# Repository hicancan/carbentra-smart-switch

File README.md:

# CARBENTRA Switch · 三路智能灯光开关

面向普通照明的三路独立远程通断工程候选。保留本地按键，使用 Wi-Fi 连接 MQTT，蓝牙负责安全配网；计量三路灯具的合计用电。外观参考用户提供的白色圆角三键开关图片，内部结构、电路和固件为独立设计。

## 从这里开始

- **构建验证**：[LOCAL_BUILD.md](LOCAL_BUILD.md)，PowerShell 7 / uv Python 3.12 / MSVC / KiCad 10 / Blender 5.2 / ESP-IDF 5.4.3。
- **改外壳**：`mechanical/` 的可编辑 Blender 源文件与参数化生成脚本
- **改电路**：KiCad 10 打开 `electronics/power.kicad_pro` 或 `electronics/control.kicad_pro`
- **查元器件**：`electronics/bom.csv`、`pinmap.csv`、`mechanical_interface.json`
- **制造与展示**：[GitHub Releases](https://github.com/hicancan/carbentra-smart-switch/releases) 提供 Gerber/钻孔、GLB/STL、图片/PDF/视频与默认禁止吸合的开发固件。
- **继续固件**：[固件说明](firmware/README.md)、[协议与条件](docs/firmware.md)、[实际目标构建报告](firmware/build-report.json)
- **安全修复复验**：[本次固件修复报告](firmware/remediation-report.json)：证书日期配置、实际 ESP32-C3 编译负控与独立 host 证书负控；不代替实物 TLS 握手或现场安全验证
- **了解电气前提**：[电路说明](docs/electronics.md)、[结构说明](mechanical/README.md)

## 已实现的范围

- 三路控制、本地按键防抖、开机先释放、上电OFF；工程构建默认禁止继电器吸合，独立编译放行与逐台commissioning后才允许ON
- 每通道15分钟手动保持、保护/维护/故障守卫，真实本地输入与独立sample序号；网络不能隐式覆盖本地保持
- Wi-Fi 与双向 TLS MQTT 远程命令；时效、序列及幂等处理
- 官方 BLE Security 2 配网，需独立的设备工厂配置；没有内嵌通用密码
- MCP39F511A 串口计量读取、校验与累计能量保存；校准缺失、数据过期或异常时不伪造读数
- 实际 ESP-IDF 5.4.3 / ESP32-C3 目标构建通过，具体结果与源/产物哈希见构建报告

共享设备语义与运行时以 [carbentra-campus-platform](https://github.com/hicancan/carbentra-campus-platform) 的 `packages/iot-contract` 和 `edge` 为唯一实现；lighting-1..3 映射为 relay.1..3，合计电量只计一次。本次 Windows 原生编译、主机回归、ERC/DRC、网络连通、8 mm 隔离与八条主电流路径检查见[验证摘要](verification/local-validation.json)。

可生成的大文件已移出 Git，构建只写指定的外部目录。电路复现边界为原生 KiCad → 严格检查 → 制造输出；旧一次性生成与自动布线工具退入 Git 历史，不承诺重新自动布线得到相同 PCB。

蓝牙在本版本中用于配网，并非另一个直接开关灯协议。计量对象是三路照明合计，不提供单路电量；开关自身待机耗电不在这条分流测量通路内。继电器软件输出状态不等于实际触点或灯具状态的独立回读。

## 尺寸与安装假设

参考图没有确认厂商型号或官方尺寸。本设计提出 86 × 86 mm 面板、9.8 mm 前部突出、74 × 70 × 34 mm 后盒，总包络为 86 × 86 × 43.8 mm。需要根据实际墙腔、螺钉与导线弯曲空间核对，不能当作所有“86底盒”通用安装承诺。

电气方案假设开关盒中具备零线，采用 220–240 V AC、50 Hz 输入。不包含单火线、调光或调色温方案；不需要把灯具回流零线接回该开关盒。

## 使用边界

这是未上电、未安装、未经过实物验证的工程文件。规则检查和成功编译不等同于电气安全、温升、浪涌、EMC、射频、灯具启动冲击或计量精度认证。制造输出不是量产放行文件，需由合格人员完成器件、装配及样机验证。

仅针对普通照明研究，不用于消防应急或其他安全关键照明。远程 OFF 不构成维修隔离；一次保护元件和最终负载能力必须按现场条件验证。

许可证范围见 [LICENSES.md](LICENSES.md)。本地 KiCad 库、SDK、厂商资料继续遵守各自许可；参见 [电路第三方说明](electronics/THIRD_PARTY.md)和[固件第三方说明](firmware/THIRD_PARTY_NOTICES.md)。

本次 Windows 固件与发布回归见 [当前固件验证](verification/current-firmware-validation.json)。打包要求当前来源和实际目标字节一致；历史 CAD/媒体复用独立标注，未重新运行实物、CAD 或渲染验收。

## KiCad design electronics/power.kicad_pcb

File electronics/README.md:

# Native editable electronics

Open the control / power `.kicad_pro` projects with KiCad 10.0.5. Schematics, routed boards, rules, local symbol/footprint libraries, BOM, pin maps and mechanical contracts are retained as editable source. These native circuit files are authoritative.

Follow [LOCAL_BUILD.md](../LOCAL_BUILD.md) and `scripts/dev.ps1 -Action electronics -BuildRoot <external-directory>`. The coordinator copies source into a fresh external directory, runs strict ERC/DRC, exports native netlists and independently compares PCB pad connections, then produces schematic PDF, Gerbers, Excellon drills and source-faithful presentation sheets. A nonzero rule check stops the workflow. Generated output and detailed JSON reports live in the build tree and Release bundle.

The export workflow also checks isolated hot/cold copper spacing and eight selected main current paths. These geometrical checks do not establish a load rating or electrical safety certification.

The validated reproducible boundary is native circuit → checks → manufacturing outputs. Earlier one-time ECO, placement-generation and autorouting scripts are retained only in Git history. Their alternate valid routings are not claimed to reproduce the current boards. After deliberate native edits, rerun the whole electronics stage and review the resulting drawings.

Third-party datasheets are linked in `reference-sources.json` and BOM/documentation rather than redistributed. Retained library files preserve their original attribution. See [THIRD_PARTY.md](THIRD_PARTY.md).

Engineering candidate only: no fabricated-board inspection, powered measurements, RF/thermal qualification or manufacturing release is implied.

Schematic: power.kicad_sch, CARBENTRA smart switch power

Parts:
C1, C2, C3, C4: 33n; C_0603_1608Metric
C5: 1u; C_0603_1608Metric
C6, C7, C8, C9, C10, C12, C14: 100n; C_0603_1608Metric
C11, C13: 10u; C_0805_2012Metric
C15: 220u 6.3V; CP_Elec_6.3x5.8
C16: 100u 10V; CP_Elec_6.3x5.8
D1, D2, D3: SS14; D_SMA
F1: T2A 277VAC / 1500A BC; UMT_H
J1: L N L1 L2 L3; TerminalBlock_Phoenix_MKDS-1,5-5-5.08_1x05_P5.08mm_Horizont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
J2: COLD LINK / JST-PH8; JST_PH_B8B-PH-K_1x08_P2.00mm_Vertical
K1, K2, K3: G5Q-1A DC5; Relay_SPST_Omron-G5Q-1A
PS1: RAC05-05SK/277; RAC05_05SK_277
Q1, Q2, Q3: AO3400A; SOT-23
R1, R2, R3: 100R; R_0603_1608Metric
R4, R5, R6: 100k; R_0603_1608Metric
R7: 2mR 4-terminal Kelvin; R_Shunt_Vishay_WSK2512_6332Metric_T2.21mm
R8, R9, R10, R15: 1k; R_0603_1608Metric
R11, R12, R13, R14: 249k; R_1206_3216Metric
R16: 10R; R_0603_1608Metric
R17, R18: 10k; R_0603_1608Metric
RV1: TMOV14RP275E; TMOV14
U2: MCP39F511A-E/MQ; QFN-28-1EP_5x5mm_P0.5mm_EP3.25x3.25mm
U3: ISOW7821DWER; ISOW7821_DWE

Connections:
C_3V3: C13.1, C14.1, C15.1, J2.3 (3V3), U3.1 (VCC), U3.7 (EN1)
C_5V: C16.1, D1.1 (K), D2.1 (K), D3.1 (K), J2.1 (5V), K1.5, K2.5, K3.5, PS1.7 (5V)
C_COIL1: D1.2 (A), K1.1, Q1.3 (D)
C_COIL2: D2.2 (A), K2.1, Q2.3 (D)
C_COIL3: D3.2 (A), K3.1, Q3.3 (D)
C_GATE1: Q1.1 (G), R1.2, R4.1
C_GATE2: Q2.1 (G), R2.2, R5.1
C_GATE3: Q3.1 (G), R3.2, R6.1
C_GND: C13.2, C14.2, C15.2, C16.2, J2.2 (GND), PS1.9 (GND_COLD), Q1.2 (S), Q2.2 (S), Q3.2 (S), R4.2, R5.2, R6.2, U3.2 (GND1), U3.8 (GND1)
C_RELAY1: J2.4 (RLY1), R1.1
C_RELAY2: J2.5 (RLY2), R2.1
C_RELAY3: J2.6 (RLY3), R3.1
C_UART_RX: J2.8 (RX), U3.4 (OUTB)
C_UART_TX: J2.7 (TX), U3.3 (INA)
H_3V3: C7.1, C11.1, C12.1, R16.1, R17.1, R18.1, U2.25 (DVDD), U3.16 (VISO)
H_AVDD: C5.1, C6.1, R16.2, U2.11 (AVDD)
H_COMMON: U2.5 (COMMONA), U2.13 (COMMONB)
H_DIV1: R11.2, R12.1
H_DIV2: R12.2, R13.1
H_DIV3: R13.2, R14.1
H_GND: C1.2, C2.2, C3.2, C4.2, C5.2, C6.2, C7.2, C8.2, C9.2, C10.2, C11.2, C12.2, F1.2, PS1.5 (AC_L), R7.1 (I_IN), R10.1, R15.2, RV1.2 (NEUTRAL), U2.20 (AN_IN), U2.21 (AGND), U2.24 (DGND), U2.27 (DGND), U2.29 (EP), U3.9 (GND2), U3.11 (SEL), U3.15 (GND2)
H_IM: C2.1, R9.2, U2.17 (I-)
H_IP: C1.1, R8.2, U2.16 (I+)
H_KELVIN_IN: R7.2 (S_IN), R9.1
H_KELVIN_OUT: R7.3 (S_OUT), R8.1
H_LOAD: K1.2, K2.2, K3.2, R7.4 (I_OUT)
H_MCLR: C10.1, R18.2, U2.26 (MCLR_N)
H_REF: C8.1, U2.23 (REF)
H_RESET: C9.1, R17.2, U2.10 (RESET_N)
H_RX: U2.4 (RX), U3.14 (OUTA)
H_TX: U2.12 (TX), U3.13 (INB)
H_VM: C3.1, R10.2, U2.18 (V-)
H_VP: C4.1, R14.2, R15.1, U2.19 (V+)
L_IN: F1.1, J1.1 (L)
L_OUT1: J1.3 (L1), K1.3
L_OUT2: J1.4 (L2), K2.3
L_OUT3: J1.5 (L3), K3.3
N_IN: J1.2 (N), PS1.1 (AC_N), R11.1, RV1.1 (LINE)

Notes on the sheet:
01 / MAINS + PROTECTION + ISOLATED PSU
02 / THREE INDEPENDENT RELAYS + DRIVERS
03 / AGGREGATE METER + REINFORCED BARRIER
CARBENTRA / SMART LIGHT SWITCH / POWER / A-CANDIDATE
DEVELOPMENT ONLY: neutral 220VAC / no dimming / no physical contact feedback / never energize this unqualified prototype
H_* is LIVE-domain. C_* is isolated control. No ground tie across barrier. ERC/DRC do not qualify mains safety.

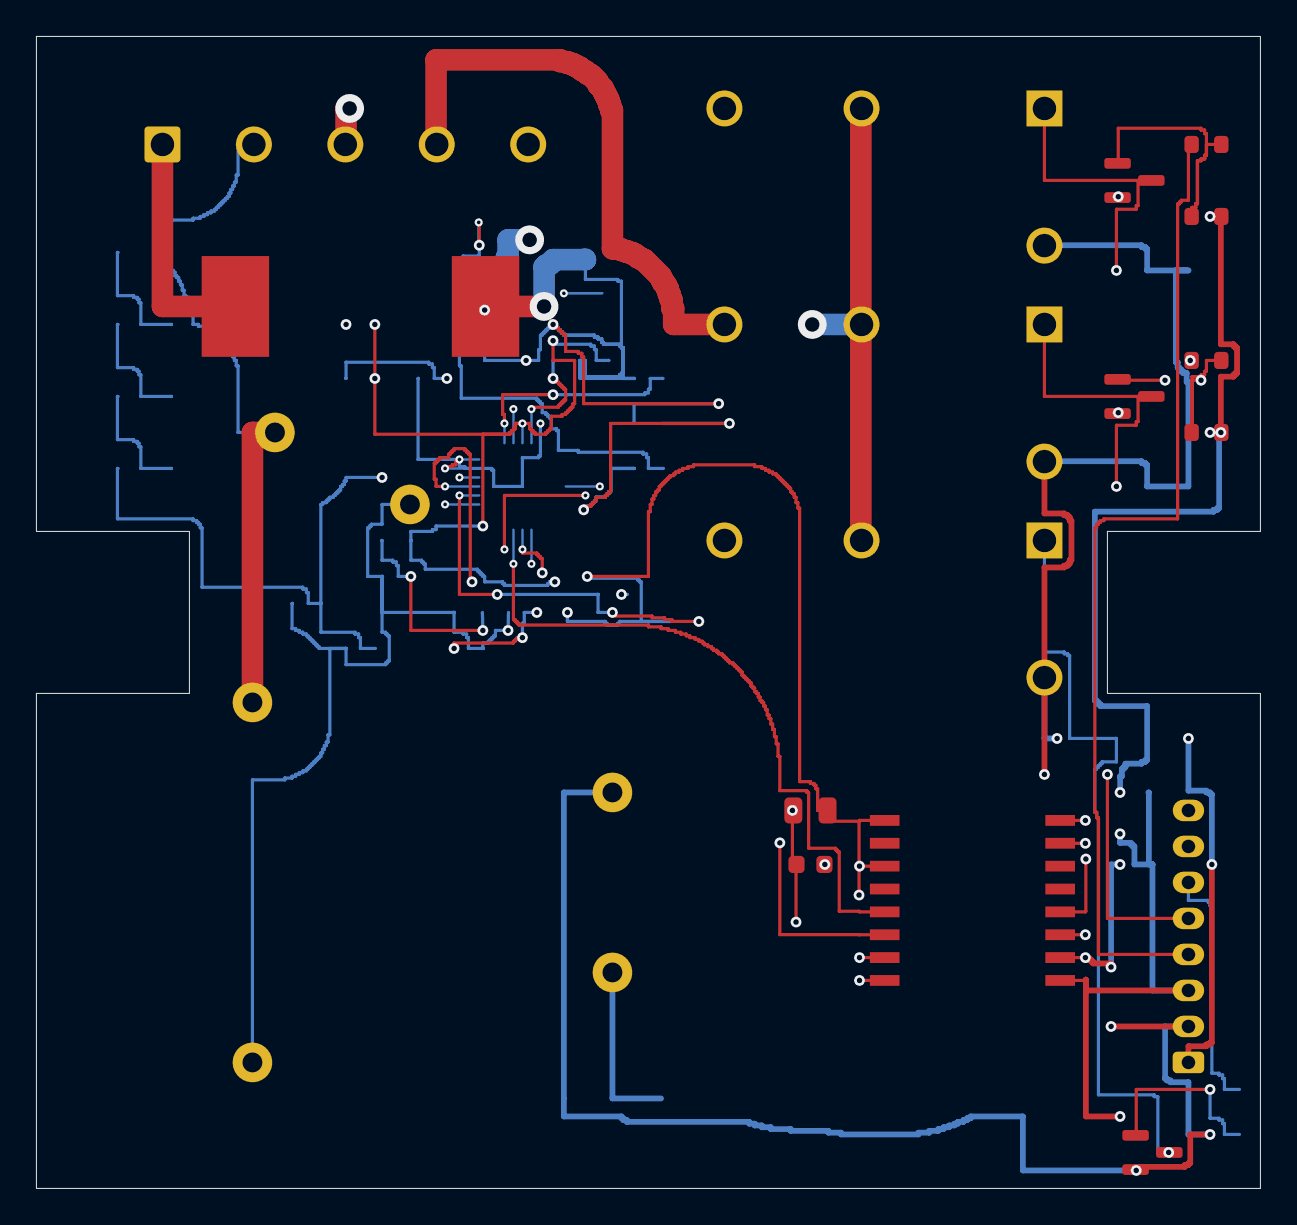
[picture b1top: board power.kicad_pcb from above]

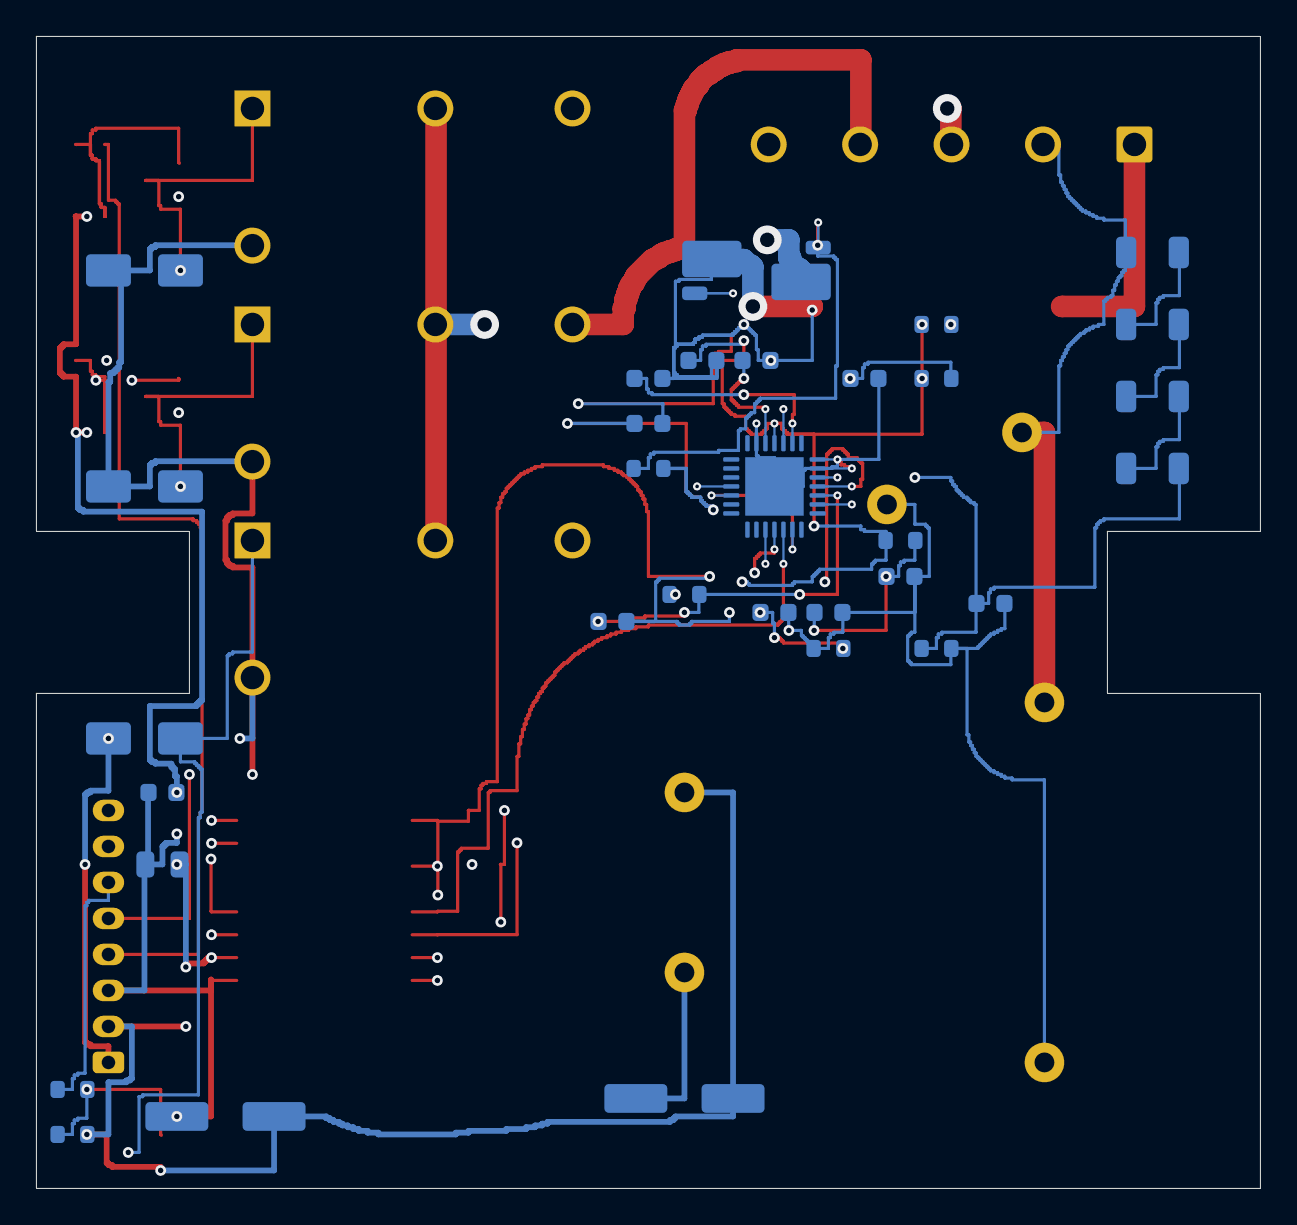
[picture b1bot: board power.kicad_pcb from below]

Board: 4 copper layers, 68.0 x 64.0 mm, 50 parts (32 on the bottom side), 38 nets.

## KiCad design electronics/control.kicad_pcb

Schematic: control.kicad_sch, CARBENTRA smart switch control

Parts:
C30: 1u; C_0603_1608Metric
C31: 10u; C_0805_2012Metric
C32, C35: 100n; C_0603_1608Metric
C33, C34: 22u; C_1206_3216Metric
C36, C37, C38: 10n; C_0603_1608Metric
J3: COLD LINK / JST-PH8; JST_PH_B8B-PH-K_1x08_P2.00mm_Vertical
R30, R31, R32, R33, R34, R35, R36: 10k; R_0603_1608Metric
SW1, SW2, SW3: B3U-1000P; SW_SPST_B3U-1000P
TP1: C_GND; TestPoint_Pad_D1.5mm
TP2: C_3V3; TestPoint_Pad_D1.5mm
TP3: C_EN; TestPoint_Pad_D1.5mm
TP4: C_BOOT; TestPoint_Pad_D1.5mm
TP5: C_U0RX; TestPoint_Pad_D1.5mm
TP6: C_U0TX; TestPoint_Pad_D1.5mm
TP7: C_USB_N; TestPoint_Pad_D1.5mm
TP8: C_USB_P; TestPoint_Pad_D1.5mm
U1: ESP32-C3-MINI-1-N4X; ESP32_C3_MINI_1
U4: TLV1117LV33DCYR; SOT-223-3_TabPin2

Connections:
C_3V3: C31.1, C32.1, C34.1, C35.1, J3.3 (3V3), R30.1, R31.1, R32.1, R33.1, R34.1, R35.1, R36.1, TP2.1, U1.3 (3V3), U4.2 (OUT/TAB)
C_5V: C33.1, J3.1 (5V), U4.3 (IN)
C_BOOT: R33.2, TP4.1, U1.23 (IO9)
C_EN: C30.1, R30.2, TP3.1, U1.8 (EN)
C_GND: C30.2, C31.2, C32.2, C33.2, C34.2, C35.2, C36.2, C37.2, C38.2, J3.2 (GND), SW1.2, SW2.2, SW3.2, TP1.1, U1.1 (GND), U1.2 (GND), U1.11 (GND), U1.14 (GND), U1.36 (GND), U1.37 (GND), U1.38 (GND), U1.39 (GND), U1.40 (GND), U1.41 (GND), U1.42 (GND), U1.43 (GND), U1.44 (GND), U1.45 (GND), U1.46 (GND), U1.47 (GND), U1.48 (GND), U1.49 (GND), U1.50 (GND), U1.51 (GND), U1.52 (GND), U1.53 (GND), U4.1 (GND)
C_KEY1: C36.1, R34.2, SW1.1, U1.18 (IO4)
C_KEY2: C37.1, R35.2, SW2.1, U1.19 (IO5)
C_KEY3: C38.1, R36.2, SW3.1, U1.20 (IO6)
C_RELAY1: J3.4 (RLY1), U1.12 (IO0)
C_RELAY2: J3.5 (RLY2), U1.13 (IO1)
C_RELAY3: J3.6 (RLY3), U1.6 (IO3)
C_STRAP2: R31.2, U1.5 (IO2)
C_STRAP8: R32.2, U1.22 (IO8)
C_U0RX: TP5.1, U1.30 (IO20)
C_U0TX: TP6.1, U1.31 (IO21)
C_UART_RX: J3.8 (RX), U1.21 (IO7)
C_UART_TX: J3.7 (TX), U1.16 (IO10)
C_USB_N: TP7.1, U1.26 (IO18)
C_USB_P: TP8.1, U1.27 (IO19)

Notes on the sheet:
04 / WI-FI + BLE RADIO + BOOT SUPPORT
05 / COLD 3.3V POWER + SERVICE + LINK
06 / THREE OFFLINE LOCAL BUTTONS
CARBENTRA / SMART LIGHT SWITCH / CONTROL / A-CANDIDATE
DEVELOPMENT ONLY: neutral 220VAC / no dimming / no physical contact feedback / never energize this unqualified prototype
H_* is LIVE-domain. C_* is isolated control. No ground tie across barrier. ERC/DRC do not qualify mains safety.

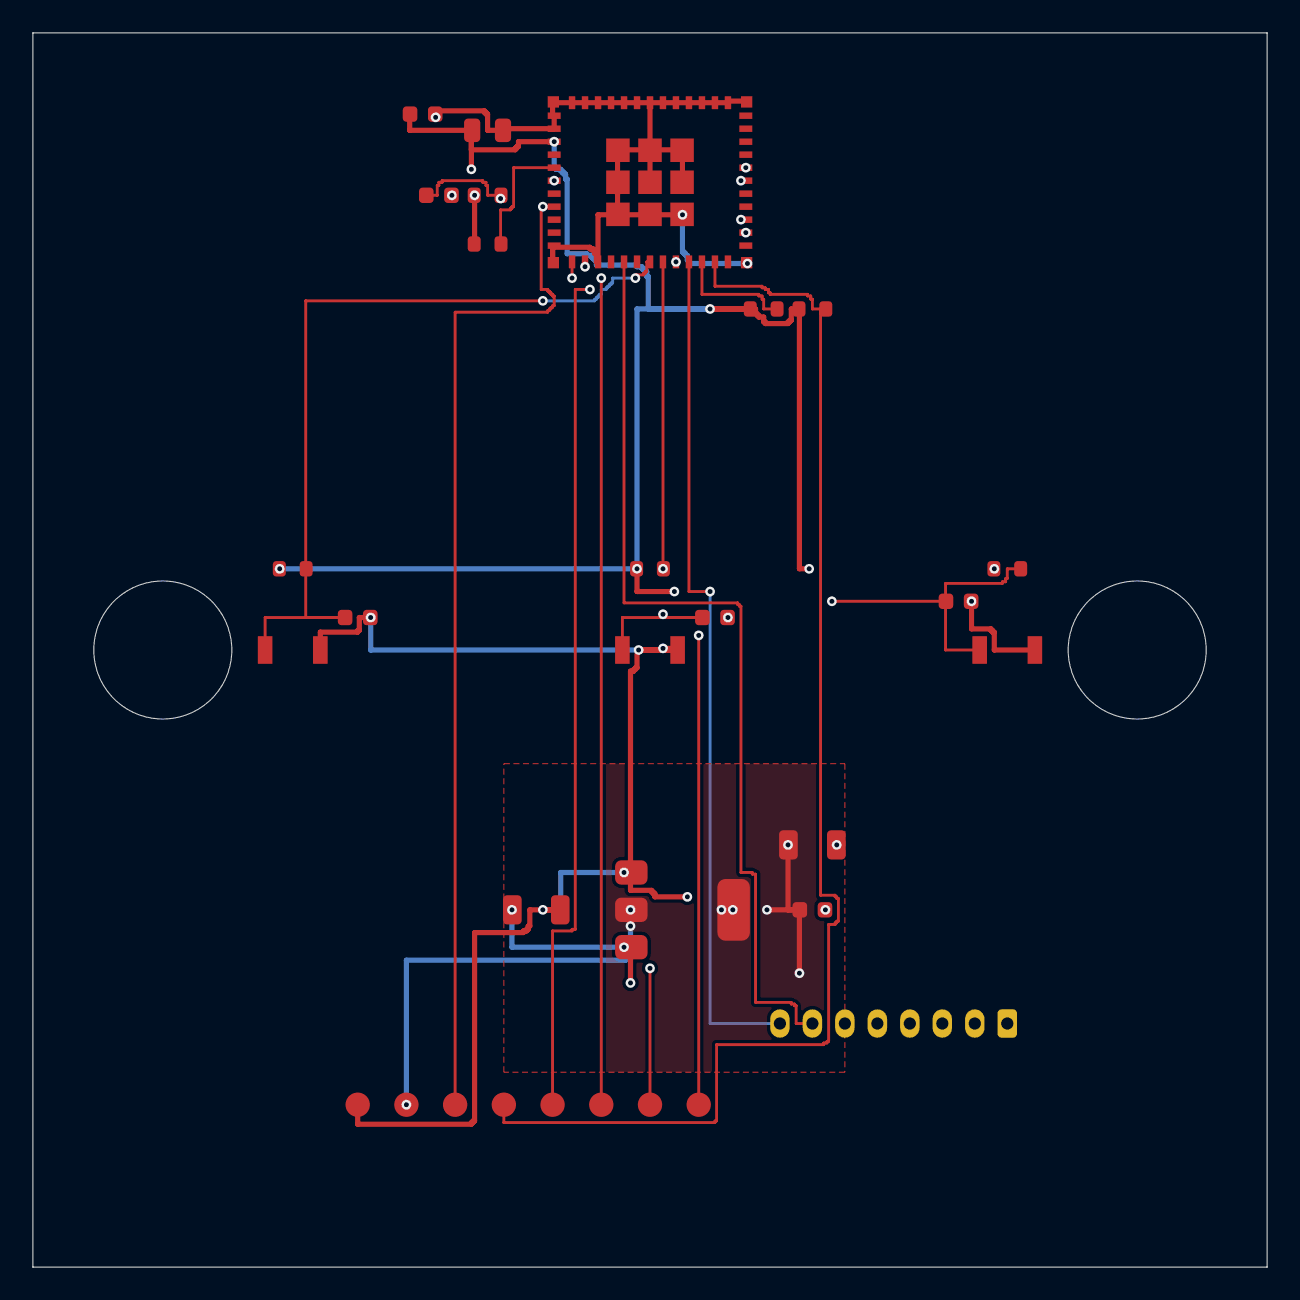
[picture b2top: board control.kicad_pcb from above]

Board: 4 copper layers, 76.0 x 76.0 mm, 32 parts (1 on the bottom side), 19 nets.

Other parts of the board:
H1, H2: MountHole8_5
